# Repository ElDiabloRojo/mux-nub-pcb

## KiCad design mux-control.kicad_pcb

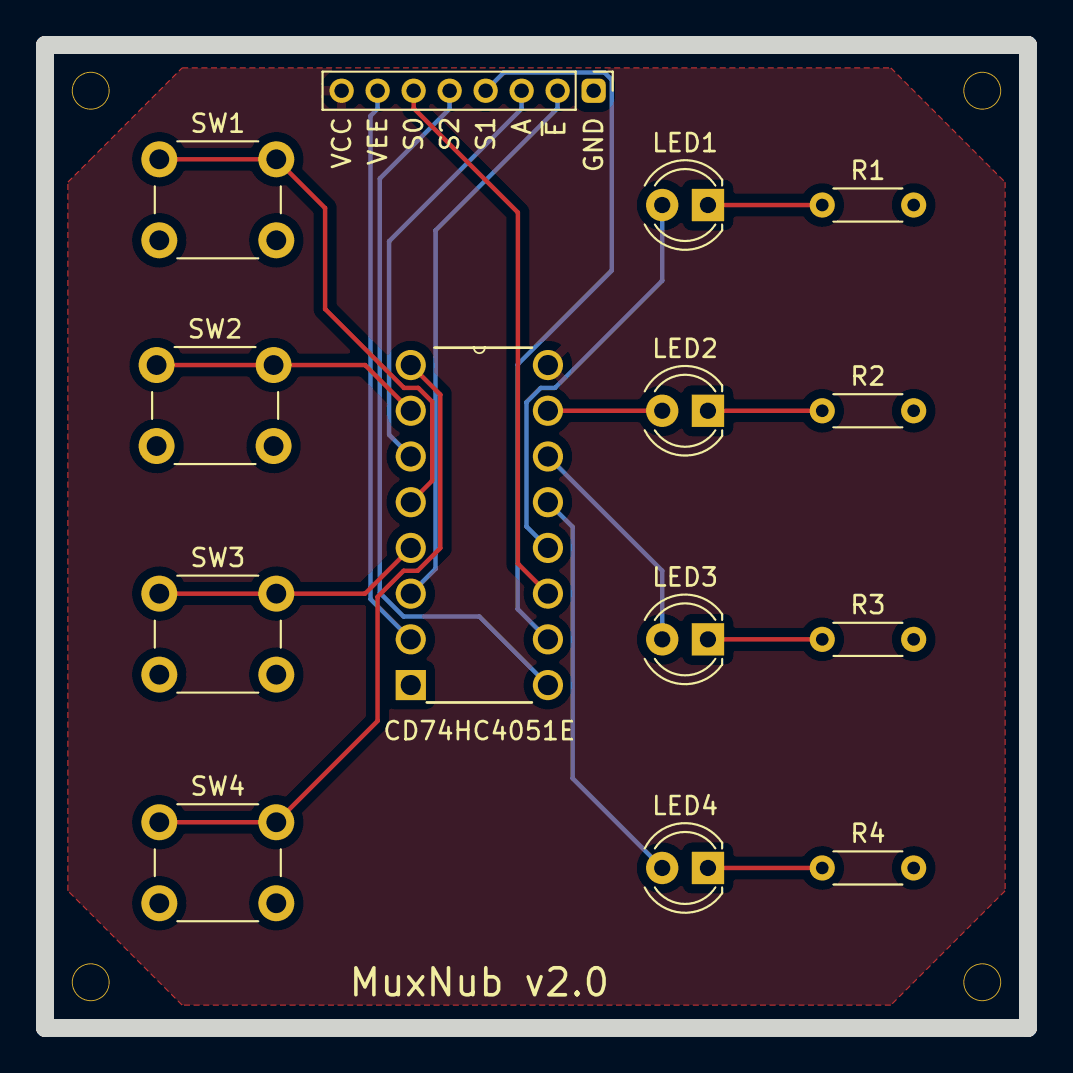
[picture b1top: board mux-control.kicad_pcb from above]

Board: 2 copper layers, 54.6 x 54.6 mm, 18 parts (0 on the bottom side), 20 nets.

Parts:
D1: LED1; LED_D4.0mm
D2: LED2; LED_D4.0mm
D3: LED3; LED_D4.0mm
D4: LED4; LED_D4.0mm
J1: Conn_01x08; PinHeader_1x08_P2.00mm_Vertical
MO1: M1; MountingHole_2.1mm
MO2, MO3, MO4: MountingHole_2.1mm
R1, R2, R3, R4: 220; R_Axial_DIN0204_L3.6mm_D1.6mm_P5.08mm_Horizontal
SW1, SW2, SW3, SW4: SW_Push_Dual; SW_PUSH_6mm_H4.3mm
U1: CD74HC4051E; DIP254P762X508-16

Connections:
unnamed: D1.1, R1.1
unnamed: D1.2, U1.12
unnamed: D2.1, R2.1
unnamed: D2.2, U1.15
unnamed: D3.1, R3.1
unnamed: D3.2, U1.14
unnamed: D4.1, R4.1
unnamed: D4.2, U1.13
unnamed: J1.GND, R1.2, R2.2, R3.2, R4.2, SW1.2, SW2.2, SW3.2, SW4.2, U1.8
unnamed: J1.~E, U1.6
unnamed: J1.3, U1.3
unnamed: J1.4, U1.10
unnamed: J1.5, U1.9
unnamed: J1.6, U1.11
unnamed: J1.7, U1.7
unnamed: J1.8, U1.16
unnamed: SW1.1, U1.4
unnamed: SW2.1, U1.2
unnamed: SW3.1, U1.5
unnamed: SW4.1, U1.1

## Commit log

2020-06-28 first draft of mux nub board
2020-06-28 removing symlinks
2020-06-28 files...
2020-06-28 autorouted
2020-07-02 new design
2020-07-02 updated freeroute tracks
2020-07-07 new board tracks required
2020-07-07 freeroute plugin pkg
2020-07-07 kicad upgraded to nightly
2020-07-07 retracking, via to s0 required ot unlock gnd plane
2020-07-08 revised v3 ready for tracking
